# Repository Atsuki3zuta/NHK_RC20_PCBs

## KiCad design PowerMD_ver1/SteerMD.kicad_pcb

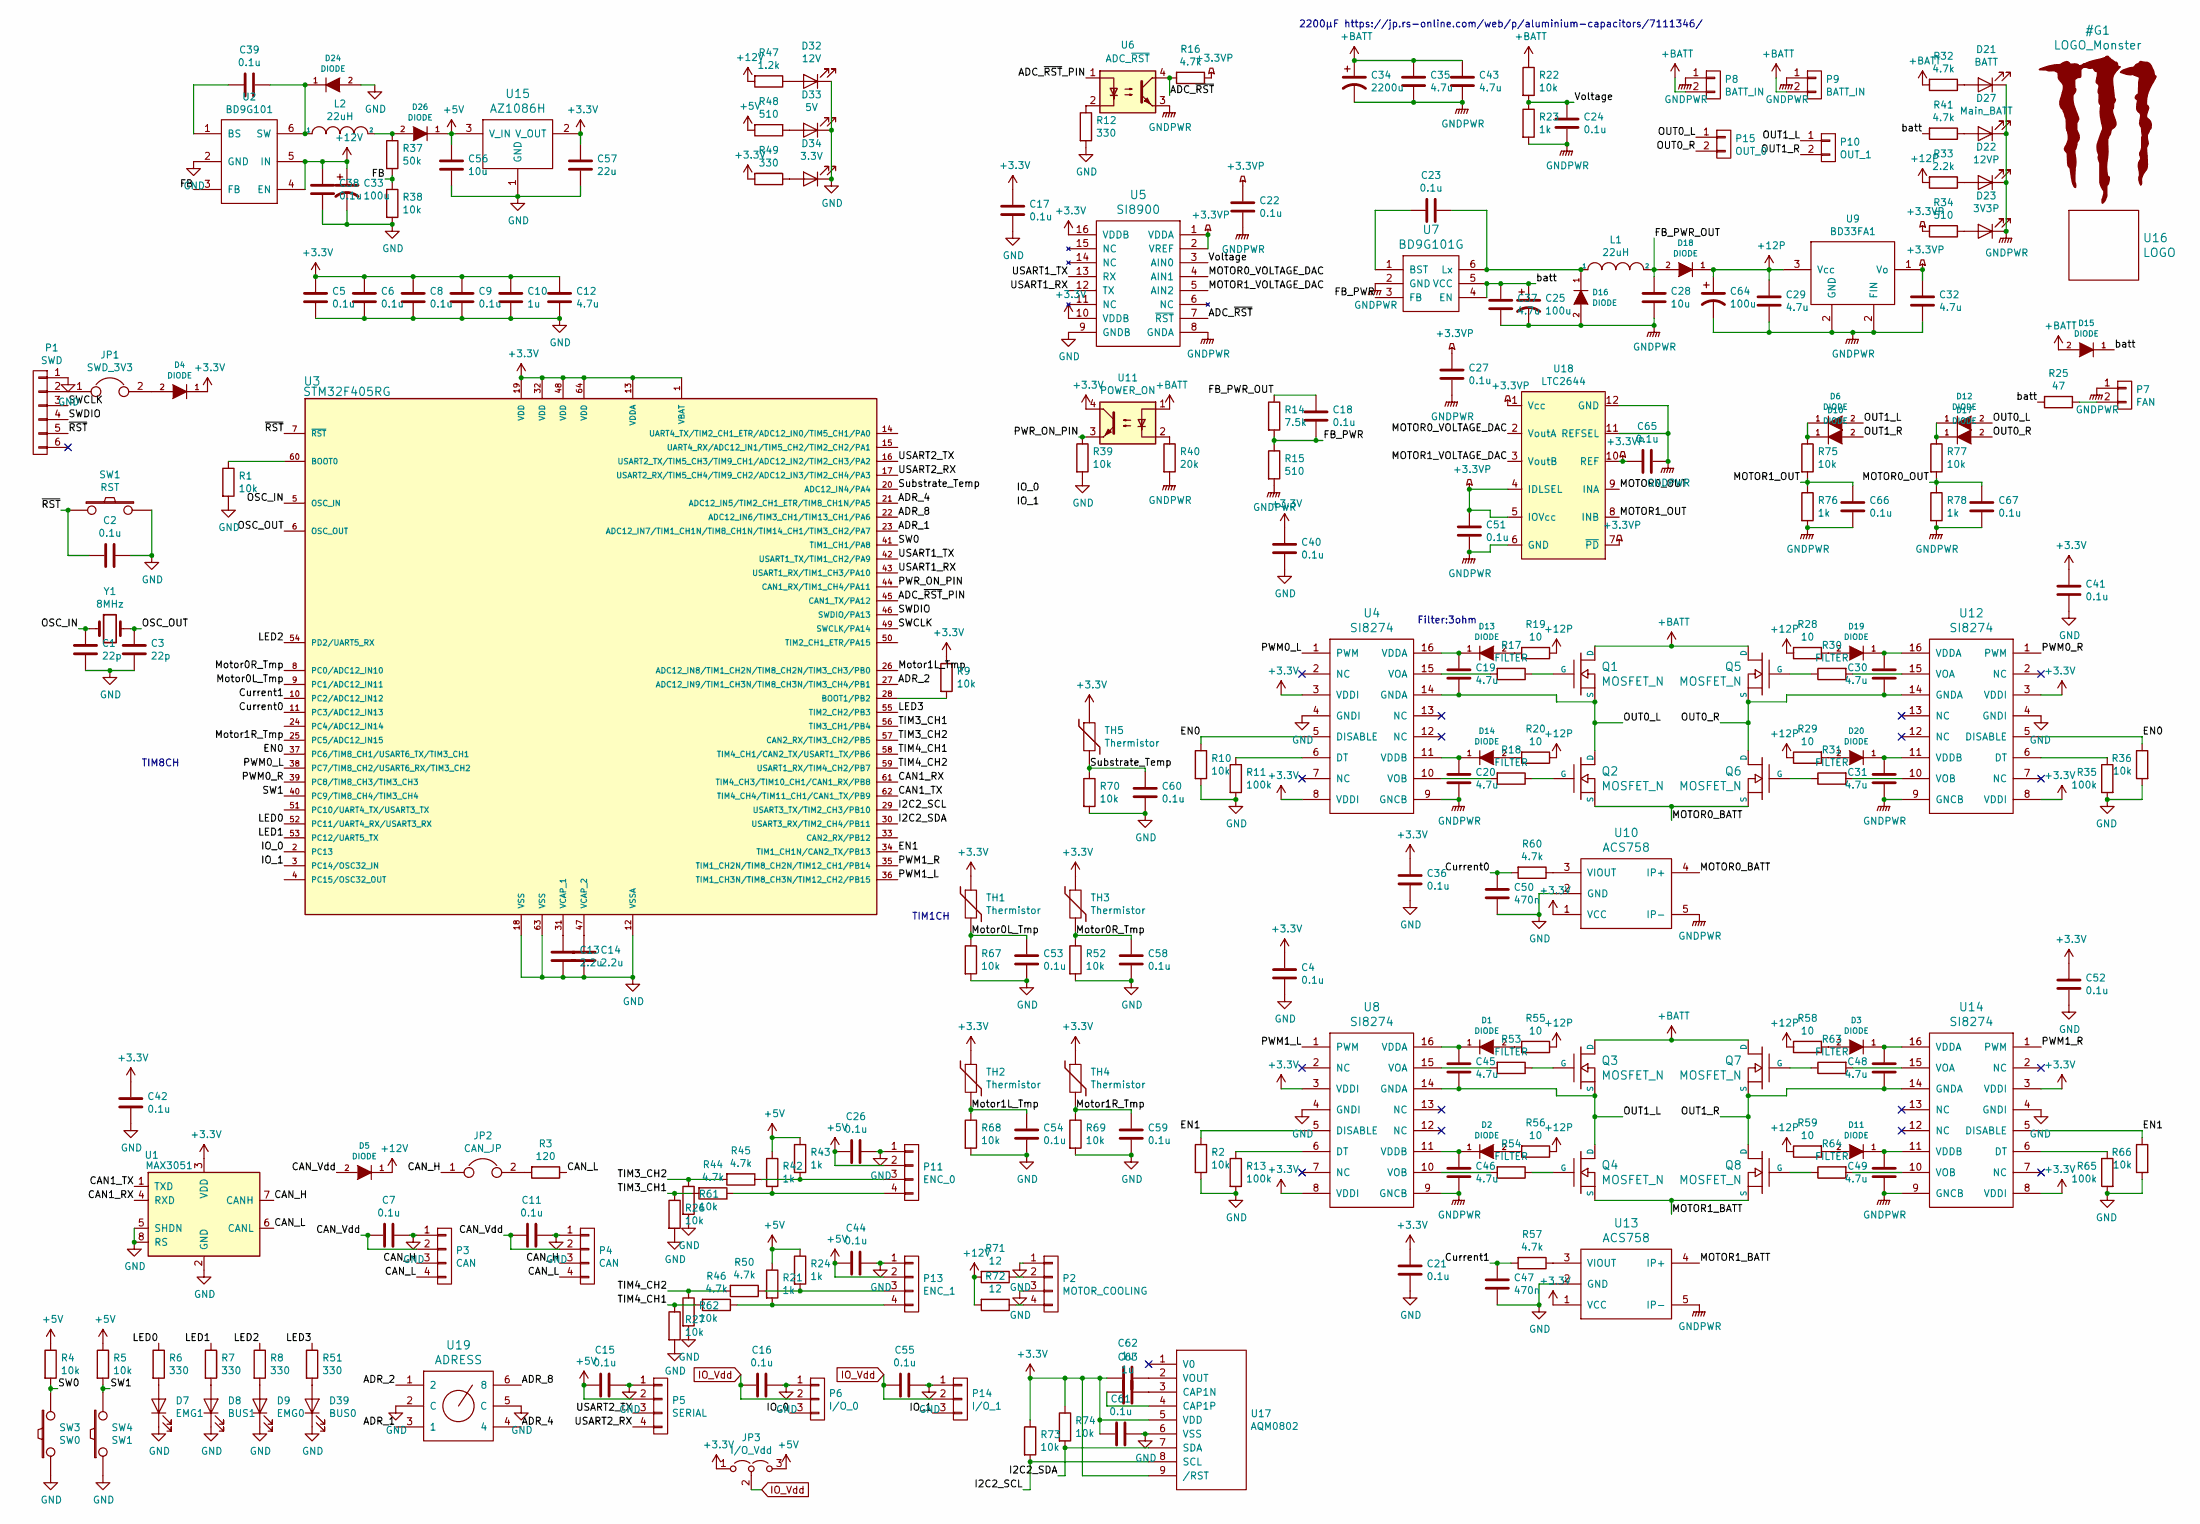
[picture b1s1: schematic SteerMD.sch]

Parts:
C1, C3: 22p; C_0603_1608Metric
C2, C5, C6, C7, C8, C9, C11, C15, C16, C18, C21, C22, C23, C24, C26, C36, C38, C39, C42, C44, C53, C54, C55, C58, C59, C60, C61: 0.1u; C_0603_1608Metric
C4, C17, C27, C40, C41, C51, C52, C65, C66, C67: 0.1u; 1608_WP
C10, C63: 1u; C_0603_1608Metric
C12: 4.7u; 1608_WP
C13, C14: 2.2u; C_0603_1608Metric
C19, C20, C30, C31, C45, C46, C48, C49: 4.7u; C_1206_3216Metric
C25, C33, C64: 100u; CP_Radial_D5.0mm_P2.50mm
C28: 10u; C_0805_2012Metric
C29, C32, C35, C37, C43: 4.7u; C_0805_2012Metric
C34: 2200u; C_Radial_D13.0mm_H25.0mm_P5.00mm
C47, C50: 470n; C_0603_1608Metric
C56: 10u; C_0603_1608Metric
C57: 22u; C_0603_1608Metric
C62: 1u; 1608_WP
D1, D2, D3, D4, D5, D6, D10, D11, D12, D13, D14, D16, D17, D18, D19, D20, D24, D26: DIODE; D_SOD-123
D7: EMG1; LED_0603_1608Metric
D8: BUS1; LED_0603_1608Metric
D9: EMG0; LED_0603_1608Metric
D15: DIODE; D_SMA
D21: BATT; LED_0603_1608Metric
D22: 12VP; LED_0603_1608Metric
D23: 3V3P; LED_0603_1608Metric
D27: Main_BATT; LED_0603_1608Metric
D32: 12V; LED_0603_1608Metric
D33: 5V; LED_0603_1608Metric
D34: 3.3V; LED_0603_1608Metric
D39: BUS0; LED_0603_1608Metric
JP1: SWD_3V3; SolderJumper-2_P1.3mm_Open_TrianglePad1.0x1.5mm
JP2: CAN_JP; PinHeader_1x02_P2.54mm_Vertical
JP3: I/O_Vdd; SW_Micro_SPST
L1, L2: 22uH; Inductor_Taiyo-Yuden_NR-60xx_HandSoldering
P1: SWD; ZH_6P
P2: MOTOR_COOLING; XA_4L
P3, P4: CAN; XA_4L
P5: SERIAL; XA_4P
P6: I/O_0; XA_3LC
P7: FAN; XA_2P
P8: BATT_IN; XT60_M
P9: BATT_IN; XT60_F
P10: OUT_1; XT60_F
P11: ENC_0; XA_4L
P13: ENC_1; XA_4L
P14: I/O_1; XA_3LC
P15: OUT_0; XT60_F
Q1, Q2, Q3, Q4, Q5, Q6, Q7, Q8: MOSFET_N; HSOF-8-1
R1, R4, R5, R9, R22, R38: 10k; R_0603_1608Metric
R2, R10, R26, R27, R36, R39, R52, R61, R62, R66, R67, R68, R69, R70, R73, R74, R75, R77: 10k; 1608_WP
R3: 120; R_0603_1608Metric
R6, R7, R8, R49, R51: 330; R_0603_1608Metric
R11, R13, R35, R65: 100k; 1608_WP
R12: 330; 1608_WP
R14: 7.5k; R_0603_1608Metric
R15, R48: 510; R_0603_1608Metric
R16, R32, R41, R57, R60: 4.7k; R_0603_1608Metric
R17, R18, R30, R31, R53, R54, R63, R64: FILTER; 1608_WP
R19, R20, R28, R29, R55, R56, R58, R59: 10; 1608_WP
R21, R24, R42, R43, R76, R78: 1k; 1608_WP
R23: 1k; R_0603_1608Metric
R25: 47; R_2812
R33: 2.2k; R_0603_1608Metric
R34: 510; 1608_WP
R37: 50k; R_0603_1608Metric
R40: 20k; R_0603_1608Metric
R44, R45, R46, R50: 4.7k; 1608_WP
R47: 1.2k; R_0603_1608Metric
R71, R72: 12; R_2812
SW1: RST; SW_SPST_CK_RS282G05A3
SW3: SW0; SW_SPST_CK_RS282G05A3
SW4: SW1; SW_SPST_CK_RS282G05A3
TH1, TH2, TH3, TH4: Thermistor; 1608_WP
TH5: Thermistor; C_0603_1608Metric
U1: MAX3051; SOIC-8_3.9x4.9mm_P1.27mm
U2: BD9G101; TSOP-6_1.65x3.05mm_P0.95mm
U3: STM32F405RG; LQFP-64_10x10mm_P0.5mm
U4, U8, U12, U14: SI8274; SOIC-16_3.9x9.9mm_P1.27mm
U5: SI8900; SOIC-16W_7.5x10.3mm_P1.27mm
U6: ADC_~RST; SO-4_4.4x2.3mm_P1.27mm
U7: BD9G101G; TSOP-6_1.65x3.05mm_P0.95mm
U9: BD33FA1; SOT-89-3
U10, U13: ACS758; ACS785xCB
U11: POWER_ON; SO-4_4.4x2.3mm_P1.27mm
U15: AZ1086H; SOT-223-3_TabPin2
U16: LOGO; Mini_Monster
U17: AQM0802; AQM0802_original
U18: LTC2644; MSOP-12_3x4mm_P0.65mm
U19: ADRESS; rotary_0F
Y1: 8MHz; Crystal_SMD_5032_2Pads

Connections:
+3.3VP: C22.1, C27.1, C32.1, C51.1, C65.2, R16.1, R34.2, U5.1 (VDDA), U5.2 (VREF), U9.1 (Vo), U18.1 (Vcc), U18.4 (IDLSEL), U18.5 (IOVcc), U18.7 (~PD), U18.10 (REF)
+3V3: C4.1, C5.1, C6.1, C8.1, C9.1, C10.1, C12.1, C17.1, C21.1, C36.1, C40.1, C41.1, C42.1, C52.1, C57.1, C61.2, C62.2, D4.1 (K), JP3.1 (A), R9.1, R49.2, R73.1, R74.1, TH1.1, TH2.1, TH3.1, TH4.1, TH5.1, U1.3 (VDD), U3.1 (VBAT), U3.13 (VDDA), U3.19 (VDD), U3.32 (VDD), U3.48 (VDD), U3.64 (VDD), U4.3 (VDDI), U4.8 (VDDI), U5.10 (VDDB), U5.16 (VDDB), U8.3 (VDDI), U8.8 (VDDI), U10.1 (VCC), U11.4, U12.3 (VDDI), U12.8 (VDDI), U13.1 (VCC), U14.3 (VDDI), U14.8 (VDDI), U15.2 (V_OUT), U17.5 (VDD), U17.9 (/RST)
+5V: C15.2, C26.2, C44.2, C56.1, D26.1 (K), JP3.3 (B), P5.2, P11.2, P13.2, R4.1, R5.1, R21.1, R24.1, R42.1, R43.1, R48.2, U15.3 (V_IN)
+12P: C29.1, C64.1, D18.1 (K), R19.1, R20.1, R28.1, R29.1, R33.2, R55.1, R56.1, R58.1, R59.1, U9.3 (Vcc)
+12V: C33.1, C38.1, D5.1 (K), R47.2, R71.2, R72.2, U2.4 (EN), U2.5 (IN)
+BATT: C34.1, C35.1, C43.1, D15.2 (A), P8.2, P9.2, Q1.D, Q3.D, Q5.D, Q7.D, R22.1, R32.2, U11.1
/ADC_~RST: R16.2, U5.7 (~RST~), U6.4
/ADC_~RST~_PIN: U3.45 (CAN1_TX/PA12), U6.1
/ADR_1: U3.23 (ADC12_IN7/TIM1_CH1N/TIM8_CH1N/TIM14_CH1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), U19.3 (1)
/ADR_2: U3.27 (ADC12_IN9/TIM1_CH3N/TIM8_CH3N/TIM3_CH4/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), U19.1 (2)
/ADR_4: U3.21 (ADC12_IN5/TIM2_CH1_ETR/TIM8_CH1N/PA5), U19.4
/ADR_8: U3.22 (ADC12_IN6/TIM3_CH1/TIM13_CH1/PA6), U19.6 (8)
/CAN1_RX: U1.4 (RXD), U3.61 (TIM4_CH3/TIM10_CH1/CAN1_RX/PB8)
/CAN1_TX: U1.1 (TXD), U3.62 (TIM4_CH4/TIM11_CH1/CAN1_TX/PB9)
/CAN_H: JP2.1, P3.3, P4.3, U1.7 (CANH)
/CAN_L: P3.4, P4.4, R3.1, U1.6 (CANL)
/CAN_Vdd: C7.2, C11.2, D5.2 (A), P3.2, P4.2
/Current0: C50.1, R60.2, U3.11 (PC3/ADC12_IN13)
/Current1: C47.1, R57.2, U3.10 (PC2/ADC12_IN12)
/EN0: R10.1, R36.1, U3.37 (PC6/TIM8_CH1/USART6_TX/TIM3_CH1), U4.5 (DISABLE), U12.5 (DISABLE)
/EN1: R2.1, R66.1, U3.34 (TIM1_CH1N/CAN2_TX/PB13), U8.5 (DISABLE), U14.5 (DISABLE)
/FB: R37.2, R38.1, U2.3 (FB)
/FB_PWR: C18.2, R14.2, R15.1, U7.3 (FB)
/FB_PWR_OUT: C18.1, C28.1, D18.2 (A), L1.2, R14.1
/I2C2_SCL: R73.2, U3.29 (USART3_TX/TIM2_CH3/PB10), U17.8 (SCL)
/I2C2_SDA: R74.2, U3.30 (USART3_RX/TIM2_CH4/PB11), U17.7 (SDA)
/IO_0: P6.3, U3.2 (PC13)
/IO_1: P14.3, U3.3 (PC14/OSC32_IN)
/LED0: R6.1, U3.52 (PC11/UART4_RX/USART3_RX)
/LED1: R7.1, U3.53 (PC12/UART5_TX)
/LED2: R8.1, U3.54 (PD2/UART5_RX)
/LED3: R51.1, U3.55 (TIM2_CH2/PB3)
/MOTOR0_BATT: Q2.S, Q6.S, U10.4 (IP+)
/MOTOR0_OUT: C67.1, R77.2, R78.1, U18.9 (INA)
/MOTOR0_VOLTAGE_DAC: U5.4 (AIN1), U18.2 (VoutA)
/MOTOR1_BATT: Q4.S, Q8.S, U13.4 (IP+)
/MOTOR1_OUT: C66.1, R75.2, R76.1, U18.8 (INB)
/MOTOR1_VOLTAGE_DAC: U5.5 (AIN2), U18.3 (VoutB)
/Motor0L_Tmp: C53.1, R67.1, TH1.2, U3.9 (PC1/ADC12_IN11)
/Motor0R_Tmp: C58.1, R52.1, TH3.2, U3.8 (PC0/ADC12_IN10)
/Motor1L_Tmp: C54.1, R68.1, TH2.2, U3.26 (ADC12_IN8/TIM1_CH2N/TIM8_CH2N/TIM3_CH3/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)
/Motor1R_Tmp: C59.1, R69.1, TH4.2, U3.25 (PC5/ADC12_IN15)
/OSC_IN: C1.2, U3.5 (OSC_IN), Y1.1
/OSC_OUT: C3.2, U3.6 (OSC_OUT), Y1.2
/OUT0_L: C19.2, D12.2 (A), P15.1, Q1.S, Q2.D, U4.14 (GNDA)
/OUT0_R: C30.2, D17.2 (A), P15.2, Q5.S, Q6.D, U12.14 (GNDA)
/OUT1_L: C45.2, D6.2 (A), P10.1, Q3.S, Q4.D, U8.14 (GNDA)
/OUT1_R: C48.2, D10.2 (A), P10.2, Q7.S, Q8.D, U14.14 (GNDA)
/PWM0_L: U3.38 (PC7/TIM8_CH2/USART6_RX/TIM3_CH2), U4.1 (PWM)
/PWM0_R: U3.39 (PC8/TIM8_CH3/TIM3_CH3), U12.1 (PWM)
/PWM1_L: U3.36 (TIM1_CH3N/TIM8_CH3N/TIM12_CH2/PB15), U8.1 (PWM)
/PWM1_R: U3.35 (TIM1_CH2N/TIM8_CH2N/TIM12_CH1/PB14), U14.1 (PWM)
/PWR_ON_PIN: R39.1, U3.44 (CAN1_RX/TIM1_CH4/PA11), U11.3
/SW0: R4.2, SW3.2, U3.41 (TIM1_CH1/PA8)
/SW1: R5.2, SW4.2, U3.40 (PC9/TIM8_CH4/TIM3_CH4)
/SWCLK: P1.3, U3.49 (SWCLK/PA14)
/SWDIO: P1.4, U3.46 (SWDIO/PA13)
/Substrate_Temp: C60.1, R70.1, TH5.2, U3.20 (ADC12_IN4/PA4)
/TIM3_CH1: R26.1, R44.2, U3.56 (TIM3_CH1/PB4)
/TIM3_CH2: R45.2, R61.1, U3.57 (CAN2_RX/TIM3_CH2/PB5)
/TIM4_CH1: R27.1, R46.2, U3.58 (TIM4_CH1/CAN2_TX/USART1_TX/PB6)
/TIM4_CH2: R50.2, R62.1, U3.59 (USART1_RX/TIM4_CH2/PB7)
/USART1_RX: U3.43 (USART1_RX/TIM1_CH3/PA10), U5.12 (TX)
/USART1_TX: U3.42 (USART1_TX/TIM1_CH2/PA9), U5.13 (RX)
/USART2_RX: P5.4, U3.17 (USART2_RX/TIM5_CH4/TIM9_CH2/ADC12_IN3/T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)
/USART2_TX: P5.3, U3.16 (USART2_TX/TIM5_CH3/TIM9_CH1/ADC12_IN2/T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)
/Voltage: C24.1, R22.2, R23.1, U5.3 (AIN0)
/batt: C25.1, C37.1, D15.1 (K), R25.2, R41.2, U7.4 (EN), U7.5 (VCC)
/~RST: C2.2, P1.5, SW1.1, U3.7 (~RST)
GND: C1.1, C2.1, C3.1, C4.2, C5.2, C6.2, C7.1, C8.2, C9.2, C10.2, C11.1, C12.2, C13.2, C14.2, C15.1, C16.1, C17.2, C21.2, C26.1, C33.2, C36.2, C38.2, C40.2, C41.2, C42.2, C44.1, C47.2, C50.2, C52.2, C53.2, C54.2, C55.1, C56.2, C57.2, C58.2, C59.2, C60.2, C61.1, D7.1 (K), D8.1 (K), D9.1 (K), D24.2 (A), D32.1 (K), D33.1 (K), D34.1 (K), D39.1 (K), P1.1, P2.1, P2.3, P3.1, P4.1, P5.1, P6.1, P11.1, P13.1, P14.1, R1.2, R2.2, R10.2, R11.2, R12.2, R13.2, R26.2, R27.2, R35.2, R36.2, R38.2, R39.2, R52.2, R61.2, R62.2, R65.2, R66.2, R67.2, R68.2, R69.2, R70.2, SW1.2, SW3.1, SW4.1, U1.2 (GND), U1.5 (SHDN), U1.8 (RS), U2.2 (GND), U3.12 (VSSA), U3.18 (VSS), U3.63 (VSS), U4.4 (GNDI), U5.9 (GNDB), U8.4 (GNDI), U10.2 (GND), U12.4 (GNDI), U13.2 (GND), U14.4 (GNDI), U15.1 (GND), U17.6 (VSS), U19.2 (C), U19.5 (C)
GNDPWR: C20.2, C22.2, C24.2, C25.2, C27.2, C28.2, C29.2, C31.2, C32.2, C34.2, C35.2, C37.2, C43.2, C46.2, C49.2, C51.2, C64.2, C65.1, C66.2, C67.2, D16.2 (A), D21.1 (K), D22.1 (K), D23.1 (K), D27.1 (K), P7.1, P8.1, P9.1, R15.2, R23.2, R40.2, R76.2, R78.2, U4.9 (GNCB), U5.8 (GNDA), U6.3, U7.2 (GND), U8.9 (GNCB), U9.2 (FIN), U10.5 (IP-), U12.9 (GNCB), U13.5 (IP-), U14.9 (GNCB), U18.6 (GND), U18.11 (REFSEL), U18.12 (GND)
IO_Vdd: C16.2, C55.2, JP3.2 (C), P6.2, P14.2
unnamed: C13.1, U3.31 (VCAP_1)
unnamed: C14.1, U3.47 (VCAP_2)
unnamed: C19.1, D13.1 (K), U4.16 (VDDA)
unnamed: C20.1, D14.1 (K), U4.11 (VDDB)
unnamed: C23.1, D16.1 (K), L1.1, U7.6 (Lx)
unnamed: C23.2, U7.1 (BST)
unnamed: C30.1, D19.1 (K), U12.16 (VDDA)
unnamed: C31.1, D20.1 (K), U12.11 (VDDB)
unnamed: C39.1, D24.1 (K), L2.1, U2.6 (SW)
unnamed: C39.2, U2.1 (BS)
unnamed: C45.1, D1.1 (K), U8.16 (VDDA)
unnamed: C46.1, D2.1 (K), U8.11 (VDDB)
unnamed: C48.1, D3.1 (K), U14.16 (VDDA)
unnamed: C49.1, D11.1 (K), U14.11 (VDDB)
unnamed: C62.1, U17.2 (VOUT)
unnamed: C63.1, U17.3 (CAP1N)
unnamed: C63.2, U17.4 (CAP1P)
unnamed: D1.2 (A), R55.2
unnamed: D2.2 (A), R56.2
unnamed: D3.2 (A), R58.2
unnamed: D4.2 (A), JP1.2
unnamed: D7.2 (A), R6.2
unnamed: D8.2 (A), R7.2
unnamed: D9.2 (A), R8.2
unnamed: D6.1 (K), D10.1 (K), R75.1
unnamed: D11.2 (A), R59.2
unnamed: D12.1 (K), D17.1 (K), R77.1
unnamed: D13.2 (A), R19.2
unnamed: D14.2 (A), R20.2
unnamed: D19.2 (A), R28.2
unnamed: D20.2 (A), R29.2
unnamed: D21.2 (A), R32.1
unnamed: D22.2 (A), R33.1
unnamed: D23.2 (A), R34.1
unnamed: D26.2 (A), L2.2, R37.1
unnamed: D27.2 (A), R41.1
unnamed: D32.2 (A), R47.1
unnamed: D33.2 (A), R48.1
unnamed: D34.2 (A), R49.1
unnamed: D39.2 (A), R51.2
unnamed: JP1.1, P1.2
unnamed: JP2.2, R3.2
unnamed: P2.2, R71.1
unnamed: P2.4, R72.1
unnamed: P7.2, R25.1
unnamed: P11.3, R43.2, R45.1
unnamed: P11.4, R42.2, R44.1
unnamed: P13.3, R24.2, R50.1
unnamed: P13.4, R21.2, R46.1
unnamed: Q1.G, R17.1
unnamed: Q2.G, R18.1
unnamed: Q3.G, R53.1
unnamed: Q4.G, R54.1
unnamed: Q5.G, R30.1
unnamed: Q6.G, R31.1
unnamed: Q7.G, R63.1
unnamed: Q8.G, R64.1
unnamed: R1.1, U3.60 (BOOT0)
unnamed: R9.2, U3.28 (BOOT1/PB2)
unnamed: R11.1, U4.6 (DT)
unnamed: R12.1, U6.2
unnamed: R13.1, U8.6 (DT)
unnamed: R17.2, U4.15 (VOA)
unnamed: R18.2, U4.10 (VOB)
unnamed: R30.2, U12.15 (VOA)
unnamed: R31.2, U12.10 (VOB)
unnamed: R35.1, U12.6 (DT)
unnamed: R40.1, U11.2
unnamed: R53.2, U8.15 (VOA)
unnamed: R54.2, U8.10 (VOB)
unnamed: R57.1, U13.3 (VIOUT)
unnamed: R60.1, U10.3 (VIOUT)
unnamed: R63.2, U14.15 (VOA)
unnamed: R64.2, U14.10 (VOB)
unnamed: R65.1, U14.6 (DT)

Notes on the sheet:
TIM1CH
TIM8CH
Filter:3ohm
2200μF https://jp.rs-online.com/web/p/aluminium-capacitors/7111346/

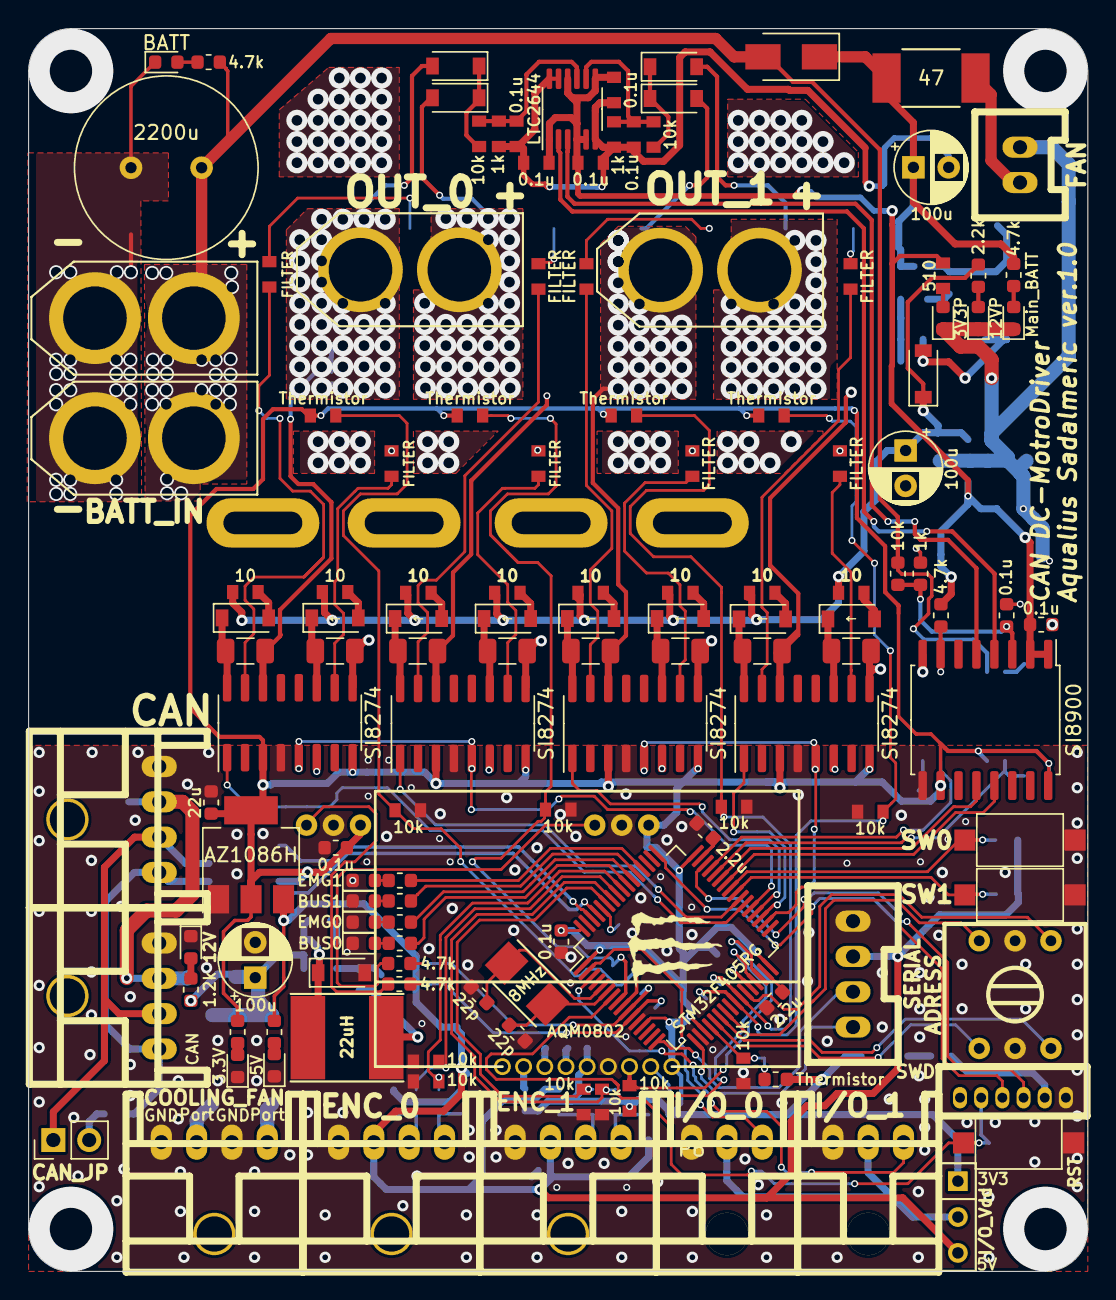
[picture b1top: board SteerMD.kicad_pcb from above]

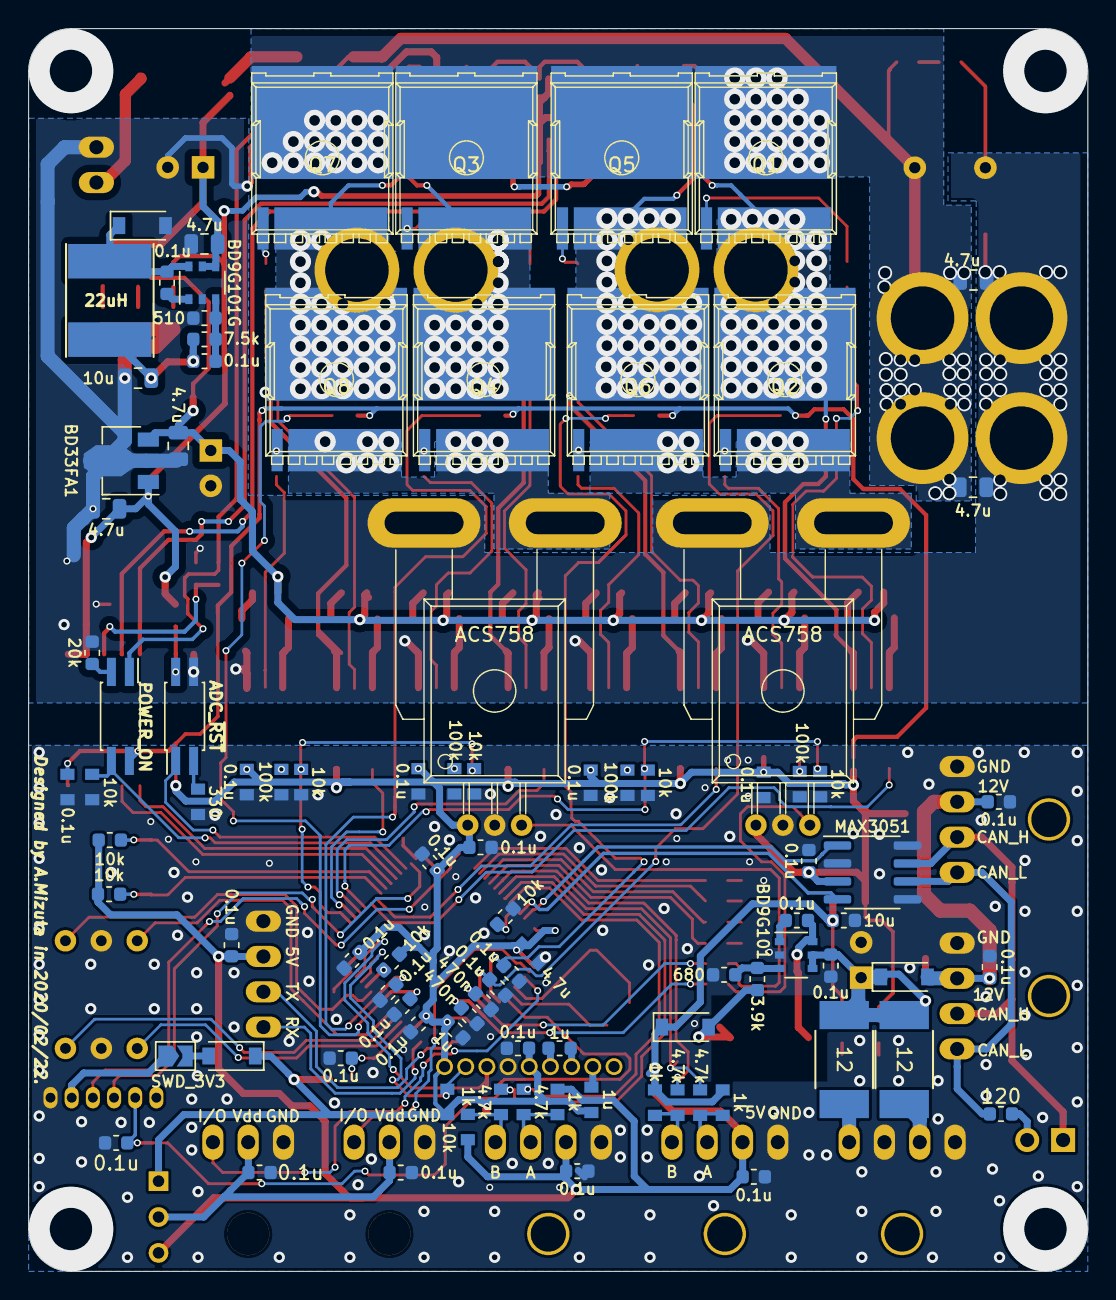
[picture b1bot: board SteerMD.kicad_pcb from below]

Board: 2 copper layers, 75.0 x 88.0 mm, 230 parts (94 on the bottom side), 147 nets.

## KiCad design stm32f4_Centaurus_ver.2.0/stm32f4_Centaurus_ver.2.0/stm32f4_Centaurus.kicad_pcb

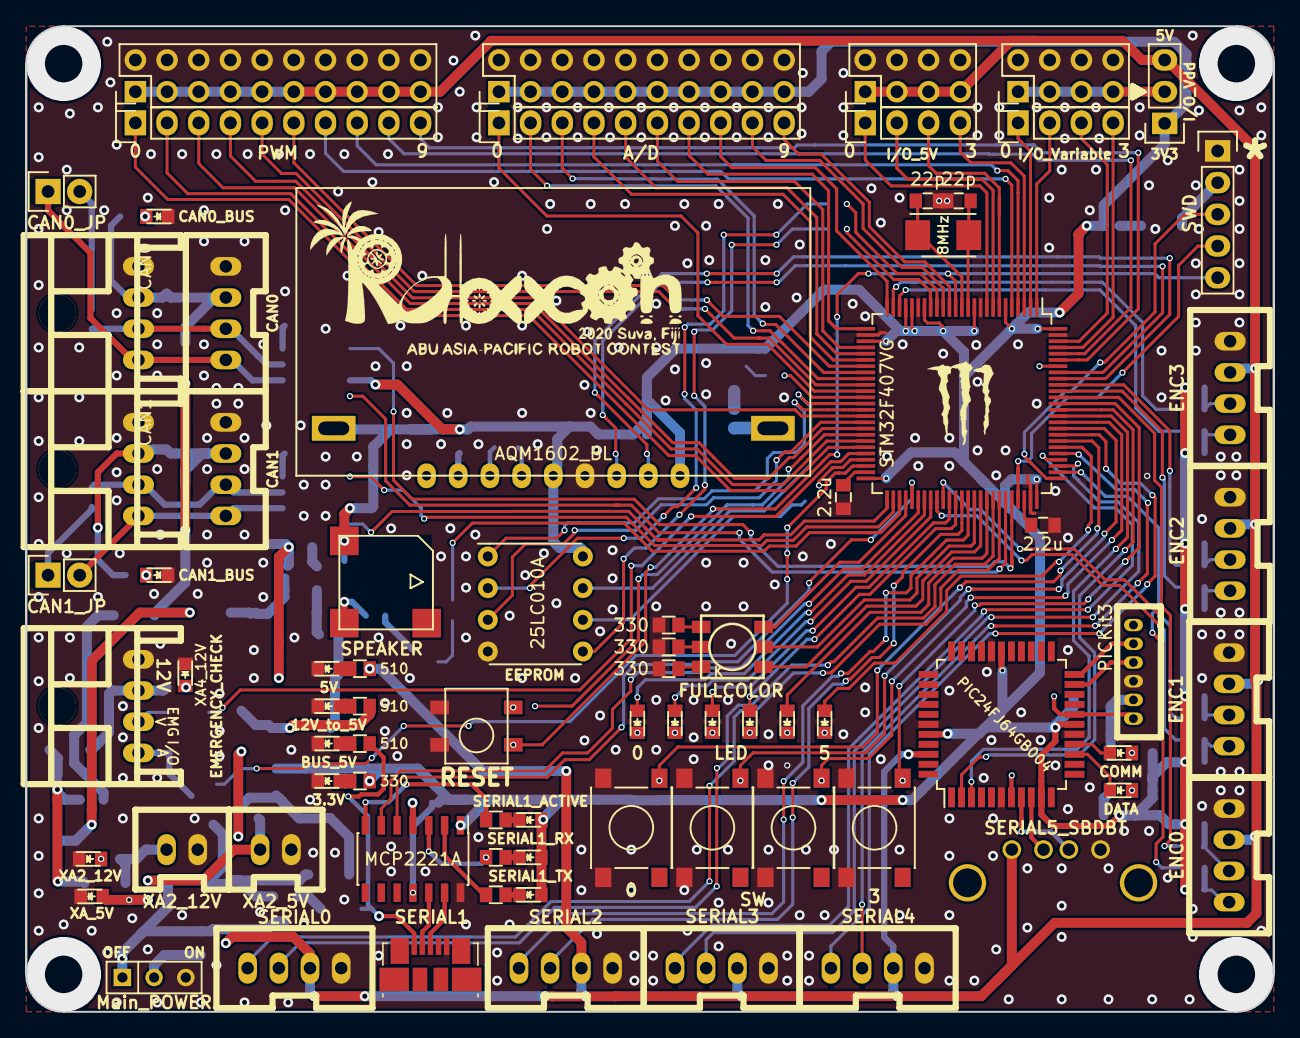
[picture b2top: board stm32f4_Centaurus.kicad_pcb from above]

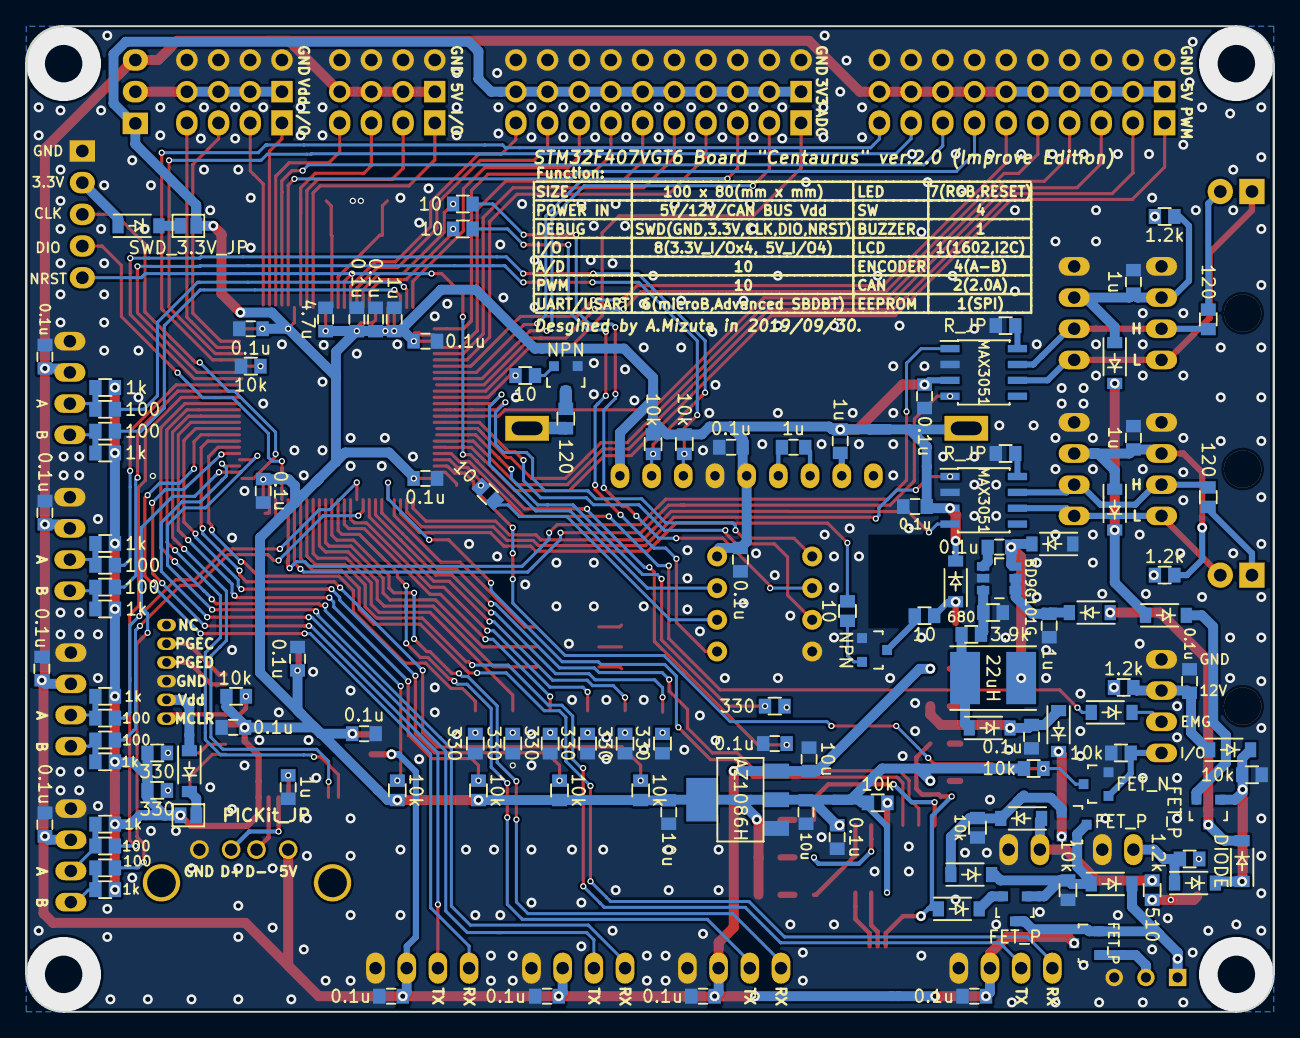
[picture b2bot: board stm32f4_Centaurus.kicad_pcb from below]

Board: 2 copper layers, 100.0 x 79.0 mm, 207 parts (127 on the bottom side), 184 nets.

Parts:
C1, C19, C22, C23, C29, C30, C34: 1u; C_0603
C2, C3, C4, C5, C8, C9, C10, C12, C14, C15, C16, C17, C18, C20, C21, C24, C25, C28, C33, C36, C37, C38, C39, C40, C41, C42: 0.1u; C_0603
C6, C7, C31: 10u; C_0603
C11, C13: 22p; C_0603
C26, C27: 2.2u; C_0603
C35: 4.7u; C_0603
D1: DATA; LED_0603
D2: COMM; LED_0603
D3: SERIAL1_TX; LED_0603
D4: SERIAL1_RX; LED_0603
D5: SERIAL1_ACTIVE; LED_0603
D6, D7, D8, D9, D10, D11, D12, D14, D15, D20, D26, D27, D28, D29, D32, D38, D39, D40: DIODE; SOD-123
D13: XA2_12V; LED_0603
D16: XA_5V; LED_0603
D17: 12V_to_5V; LED_0603
D18: BUS_5V; LED_0603
D19, D21, D22, D23, D24, D25: LED; LED_0603
D30: 5V; LED_0603
D31: 3.3V; LED_0603
D35: XA4_12V; LED_0603
D36: CAN0_BUS; LED_0603
D37: CAN1_BUS; LED_0603
IC1: PIC24FJ64GB004; LQFP-44_10x10mm_Pitch0.8mm
JP1: CAN0_JP; Pin_Header_Straight_1x02
JP2: CAN1_JP; Pin_Header_Straight_1x02
JP3: SWD_3.3V_JP; GS2
JP4: PICKit_JP; GS2
JP5: I/O_Vdd; Pin_Header_Straight_1x03
L1: 22uH; Inductor_Taiyo-Yuden_NR-50xx_HandSoldering
LED1: RESET; TSHD
P1: PICKit3; ZH_6T
P2: SERIAL5_SBDBT; USB_A
P3: ENC0; XA_4T
P4: ENC2; XA_4T
P5: SERIAL1; USB_Micro-B_Molex_47346-0001
P6: ENC3; XA_4T
P7: ENC1; XA_4T
P8: SERIAL4; XA_4T
P9: SERIAL3; XA_4T
P10: XA2_12V; XA_2T
P11: CAN0; XA_4T
P12: CAN1; XA_4T
P13: CAN0; XA_4LC
P14: CAN1; XA_4LC
P15: SERIAL2; XA_4T
P16: SERIAL0; XA_4T
P17: XA2_5V; XA_2T
P18: SWD; Pin_Header_Straight_1x05
P23: A/D; Pin_Header_Straight_1x10
P24: PWM; Pin_Header_Straight_1x10
P25: A/D_batt; Pin_Header_Straight_2x10
P26: PWM_batt; Pin_Header_Straight_2x10
P27: EMERGENCY_CHECK; XA_4LC
P28: I/O_5V; Pin_Header_Straight_1x04
P29: I/O_Variable; Pin_Header_Straight_1x04
P30: I/O_5V_batt; Pin_Header_Straight_2x04
P31: I/O_Variable; Pin_Header_Straight_2x04
Q1, Q2, Q3, Q6: FET_P; SOT-23
Q4, Q5: NPN; SOT-123
Q7: FET_N; SOT-23
R1, R12, R25, R26, R28, R30, R45, R50, R52, R54, R55, R56, R69, R71: 10k; R_0603
R2, R3, R17, R22, R23, R24, R46, R47, R48, R49, R57, R58, R59, R60, R61, R72: 330; R_0603
R4, R5, R6, R7, R13, R14, R15, R16: 100; R_0603
R8, R9, R10, R11, R18, R19, R20, R21: 1k; R_0603
R33, R66, R67, R68: 1.2k; R_0603
R34, R37, R44, R65: 510; R_0603
R35: 3.9k; R_0603
R36: 680; R_0603
R38, R39: R_JP; R_0603
R40, R41, R43: 120; R_0603
R42, R51, R53, R62, R63, R64: 10; R_0603
SP1: SPEAKER; UGCT7525AN4
SW1: Main_POWER; SW_Micro_SPST
SW2: SW1; SW_SPST_PTS645
SW3: SW0; SW_SPST_PTS645
SW4: SW2; SW_SPST_PTS645
SW5: SW3; SW_SPST_PTS645
U1: STM32F407VG; TQFP-100_14x14mm_Pitch0.5mm
U2: AZ1086H
U3: MCP2221A; SOIC-14_3.9x8.7mm_Pitch1.27mm
U4: BD9G101G; TSOT-6-MK06A
U5, U6: MAX3051; SOIC-8_3.9x4.9mm_Pitch1.27mm
U7: AQM1602_BL; AQM1602_BL_Fad
U8: OSTBABS4C2B
U9: LOGO; Mini_Monster
U10: LOGO; kitLogo_Mask_5.0x5.0
U12: 25LC010A; DIP-8_W7.62mm
U13: LOGO; Robocon2020_30.0x12.5_silk
X1: 8MHz; Crystal_SMD_5032_2Pads

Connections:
+3V3: C2.2, C3.1, C4.1, C7.1, C10.1, C20.2, C21.2, C28.2, C29.2, C31.1, C33.1, C34.1, C35.1, C36.1, C37.1, C38.1, C39.1, C40.1, C41.2, D3.1, D4.1, D5.1, D20.2, IC1.10, IC1.17, IC1.28, IC1.40, JP3.1, JP4.1, JP5.1, P25.1, P25.3, P25.5, P25.7, P25.9, P25.11, P25.13, P25.15, P25.17, P25.19, R1.2, R2.1, R3.1, R8.2, R9.2, R10.2, R11.2, R12.2, R18.2, R19.2, R20.2, R21.2, R45.1, R50.1, R52.1, R54.1, R55.1, R56.1, R69.1, R72.2, SP1.1, U1.6, U1.11, U1.19, U1.21, U1.22, U1.28, U1.50, U1.75, U1.100, U2.2, U3.1, U3.11, U5.3, U6.3, U7.5, U7.9, U7.10, U12.8
+5V: C6.1, C8.2, C9.2, C14.2, C15.2, C16.2, C17.2, C24.2, C25.2, IC1.42, JP5.3, P2.1, P3.2, P4.2, P6.2, P7.2, P8.2, P9.2, P15.2, P16.2, P26.1, P26.3, P26.5, P26.7, P26.9, P26.11, P26.13, P26.15, P26.17, P26.19, P30.1, P30.3, P30.5, P30.7, Q6.3, R65.2, U2.3
+12V: D6.2, D29.1, Q1.3
/12V_TO_5V: C5.1, D10.1, D15.2, R37.2
/ADC12_IN2: P23.8, U1.25
/ADC12_IN3: P23.7, U1.26
/ADC12_IN4: P23.6, U1.29
/ADC12_IN5: P23.5, U1.30
/ADC12_IN6: P23.4, U1.31
/ADC12_IN9: P23.1, U1.36
/ADC12_IN10: P23.10, U1.15
/ADC12_IN11: P23.9, U1.16
/ADC12_IN14: P23.3, U1.33
/ADC12_IN15: P23.2, U1.34
/BUS_5V: D12.1, P5.1, R44.2
/CAN0_H: P11.3, P13.3, R40.1, U5.7
/CAN0_L: JP1.1, P11.4, P13.4, U5.6
/CAN1_H: P12.3, P14.3, R41.2, U6.7
/CAN1_L: JP2.2, P12.4, P14.4, U6.6
/CAN1_RX: U1.70, U5.4
/CAN1_TX: U1.71, U5.1
/CAN2_RX: U1.51, U6.4
/CAN2_TX: U1.52, U6.1
/CAN_BUS_12V: D7.1, D38.2, D39.2
/D+: IC1.8, P2.3
/D+_USB: P5.3, U3.13
/D-: IC1.9, P2.2
/D-_USB: P5.2, U3.12
/FB: R35.2, R36.1, U4.3
/GP0: R22.2, U3.2
/GP1: R23.2, U3.3
/GP2: R24.2, U3.7
/I2C1_SCL: R52.2, U1.92, U7.8
/I2C1_SDA: R50.2, U1.93, U7.7
/MCLR: IC1.18, P1.1, R1.1
/NRST: C12.1, LED1.1, P18.5, U1.14
/OSC_IN: C13.1, U1.12, X1.2
/OSC_OUT: C11.1, U1.13, X1.1
/PA8: D23.1, U1.67
/PB2: R42.2, U1.37
/PB11: Q7.3, R69.2, U1.48
/PC13: P28.3, U1.7
/PC14: P28.2, U1.8
/PC15: P28.1, U1.9
/PD0: D25.1, U1.81
/PD1: R54.2, SW3.2, U1.82
/PD3: R45.2, SW2.2, U1.84
/PD4: R55.2, SW4.2, U1.85
/PD7: R56.2, SW5.2, U1.88
/PD10: D19.1, U1.57
/PD11: D21.1, U1.58
/PD14: D22.1, U1.61
/PD15: D24.1, U1.62
/PE0: P29.4, U1.97
/PE1: P29.3, U1.98
/PE2: P29.2, U1.1
/PE3: P29.1, U1.2
/PE4: P28.4, U1.3
/PE7: U1.38, U12.7
/PE8: U1.39, U12.1
/PE10: U1.41, U12.3
/PE12: R17.1, U1.43
/PE15: D26.1, U1.46
/PGEC1: IC1.22, P1.5
/PGED1: IC1.21, P1.4
/SPI2_MISO: R62.2, U1.17
/SPI2_MOSI: R64.1, U1.18
/SPI2_SCK: R63.1, U1.47
/SWCLK: P18.3, U1.76
/SWDIO: P18.4, U1.72
/TIM1_CH1: P24.4, U1.40
/TIM1_CH2: P24.3, U1.42
/TIM1_CH3: P24.2, U1.44
/TIM1_CH4: P24.1, U1.45
/TIM2_CH1: R5.2, U1.77
/TIM2_CH2: R4.2, U1.89
/TIM3_CH1: R7.2, U1.90
/TIM3_CH2: R6.2, U1.91
/TIM4_CH1: R16.2, U1.59
/TIM4_CH2: R15.2, U1.60
/TIM5_CH1: R14.2, U1.23
/TIM5_CH2: R13.2, U1.24
/TIM8_CH1: P24.6, U1.32
/TIM8_CH2: P24.5, U1.35
/TIM8_CH3: U1.65, U8.2
/TIM8_CH4: U1.66, U8.1
/TIM9_CH1: P24.8, U1.4
/TIM9_CH2: P24.7, U1.5
/TIM10_CH1: P24.10, U1.95
/TIM11_CH1: P24.9, U1.96
/TIM12_CH1: R51.2, U1.53
/TIM12_CH2: U1.54, U8.3
/UART4_RX: P9.4, U1.79
/UART4_TX: P9.3, U1.78
/UART5_RX: P8.4, U1.83
/UART5_TX: P8.3, U1.80
/USART1_RX: P16.4, U1.69
/USART1_TX: P16.3, U1.68
/USART2_RX: IC1.2, U1.87
/USART2_TX: IC1.3, U1.86
/USART3_RX: U1.56, U3.6
/USART3_TX: U1.55, U3.5
/USART6_RX: P15.4, U1.64
/USART6_TX: P15.3, U1.63
/XA_12V: D6.1, D8.2, D32.2, Q1.1, R26.1
CAN0_BUS_Vdd: C22.2, D38.1, P11.2, P13.2, R67.2
CAN1_BUS_Vdd: C23.2, D39.1, P12.2, P14.2, R68.2
GND: C1.2, C2.1, C3.2, C4.2, C5.2, C6.2, C7.2, C8.1, C9.1, C10.2, C11.2, C12.2, C13.2, C14.1, C15.1, C16.1, C17.1, C19.2, C20.1, C21.1, C22.1, C23.1, C24.1, C25.1, C26.2, C27.2, C28.1, C31.2, C33.2, C34.2, C35.2, C36.2, C37.2, C38.2, C39.2, C40.2, C41.1, C42.1, D13.2, D14.1, D16.2, D17.2, D18.2, D30.2, D31.2, D35.2, D36.2, D37.2, IC1.6, IC1.16, IC1.29, IC1.39, LED1.2, LED1.4, P1.3, P2.4, P3.1, P4.1, P5.5, P6.1, P7.1, P8.1, P9.1, P10.1, P11.1, P12.1, P13.1, P14.1, P15.1, P16.1, P17.1, P18.1, P25.2, P25.4, P25.6, P25.8, P25.10, P25.12, P25.14, P25.16, P25.18, P25.20, P26.2, P26.4, P26.6, P26.8, P26.10, P26.12, P26.14, P26.16, P26.18, P26.20, P27.1, P30.2, P30.4, P30.6, P30.8, P31.2, P31.4, P31.6, P31.8, Q4.2, Q5.2, Q7.2, R25.2, R26.2, R28.2, R30.2, R36.2, R38.1, R39.1, R46.1, R47.1, R48.1, R49.2, R57.2, R58.2, R59.2, R60.2, R61.2, R71.2, SW1.3, SW2.1, SW3.1, SW4.1, SW5.1, U1.10, U1.20, U1.27, U1.74, U1.99, U2.1, U3.14, U4.2, U5.2, U6.2, U7.6, U12.4
unnamed: C1.1, IC1.7
unnamed: C18.1, D14.2, L1.1, U4.6
unnamed: C18.2, U4.1
unnamed: C19.1, D29.2, U4.4, U4.5
unnamed: C26.1, U1.49
unnamed: C27.1, U1.73
unnamed: C29.1, U7.2
unnamed: C30.1, U7.3
unnamed: C30.2, U7.4
unnamed: D1.1, R2.2
unnamed: D1.2, IC1.14
unnamed: D2.1, R3.2
unnamed: D2.2, IC1.15
unnamed: D3.2, R22.1
unnamed: D4.2, R23.1
unnamed: D5.2, R24.1
unnamed: D7.2, Q1.2
unnamed: D10.2, Q2.2
unnamed: D9.1, D11.2, Q2.1, R28.1
unnamed: D12.2, Q3.2
unnamed: D13.1, R33.1
unnamed: D15.1, L1.2, R35.1
unnamed: D16.1, R34.1
unnamed: D17.1, R37.1
unnamed: D18.1, R44.1
unnamed: D19.2, R49.1
unnamed: D20.1, R53.1, SP1.2
unnamed: D21.2, R57.1
unnamed: D22.2, R58.1
unnamed: D23.2, R59.1
unnamed: D24.2, R60.1
unnamed: D25.2, R61.1
unnamed: D26.2, P27.3
unnamed: D9.2, D27.1, Q2.3, Q3.1, R30.1
unnamed: D27.2, Q3.3, Q6.2, SW1.1
unnamed: D28.1, P1.2
unnamed: D28.2, JP4.2
unnamed: D30.1, R65.1
unnamed: D31.1, R72.1
unnamed: D35.1, R66.1
unnamed: D36.1, R67.1
unnamed: D37.1, R68.1
unnamed: D40.1, P18.2
unnamed: D40.2, JP3.2
unnamed: JP1.2, R40.2
unnamed: JP2.1, R41.1
unnamed: JP5.2, P31.1, P31.3, P31.5, P31.7
unnamed: LED1.3, R17.2
unnamed: P3.3, R4.1, R10.1
unnamed: P3.4, R5.1, R8.1
unnamed: P4.3, R6.1, R11.1
unnamed: P4.4, R7.1, R9.1
unnamed: P6.3, R13.1, R20.1
unnamed: P6.4, R14.1, R18.1
unnamed: P7.3, R15.1, R21.1
unnamed: P7.4, R16.1, R19.1
unnamed: P27.4, Q7.1, R71.1
unnamed: Q4.1, R51.1
unnamed: Q4.3, R53.2
unnamed: Q5.1, R42.1
unnamed: Q5.3, R43.2
unnamed: Q6.1, SW1.2
unnamed: R12.1, U3.4
unnamed: R25.1, U1.94
unnamed: R38.2, U5.8
unnamed: R39.2, U6.8
unnamed: R43.1, U7.11
unnamed: R46.2, U8.6
unnamed: R47.2, U8.5
unnamed: R48.2, U8.4
unnamed: R62.1, U12.2
unnamed: R63.2, U12.6
unnamed: R64.2, U12.5
XA2_5V: D11.1, P17.2, R34.2
XA2_12V: D8.1, P10.2, R33.2
XA4_12V: C42.2, D32.1, P27.2, R66.2
